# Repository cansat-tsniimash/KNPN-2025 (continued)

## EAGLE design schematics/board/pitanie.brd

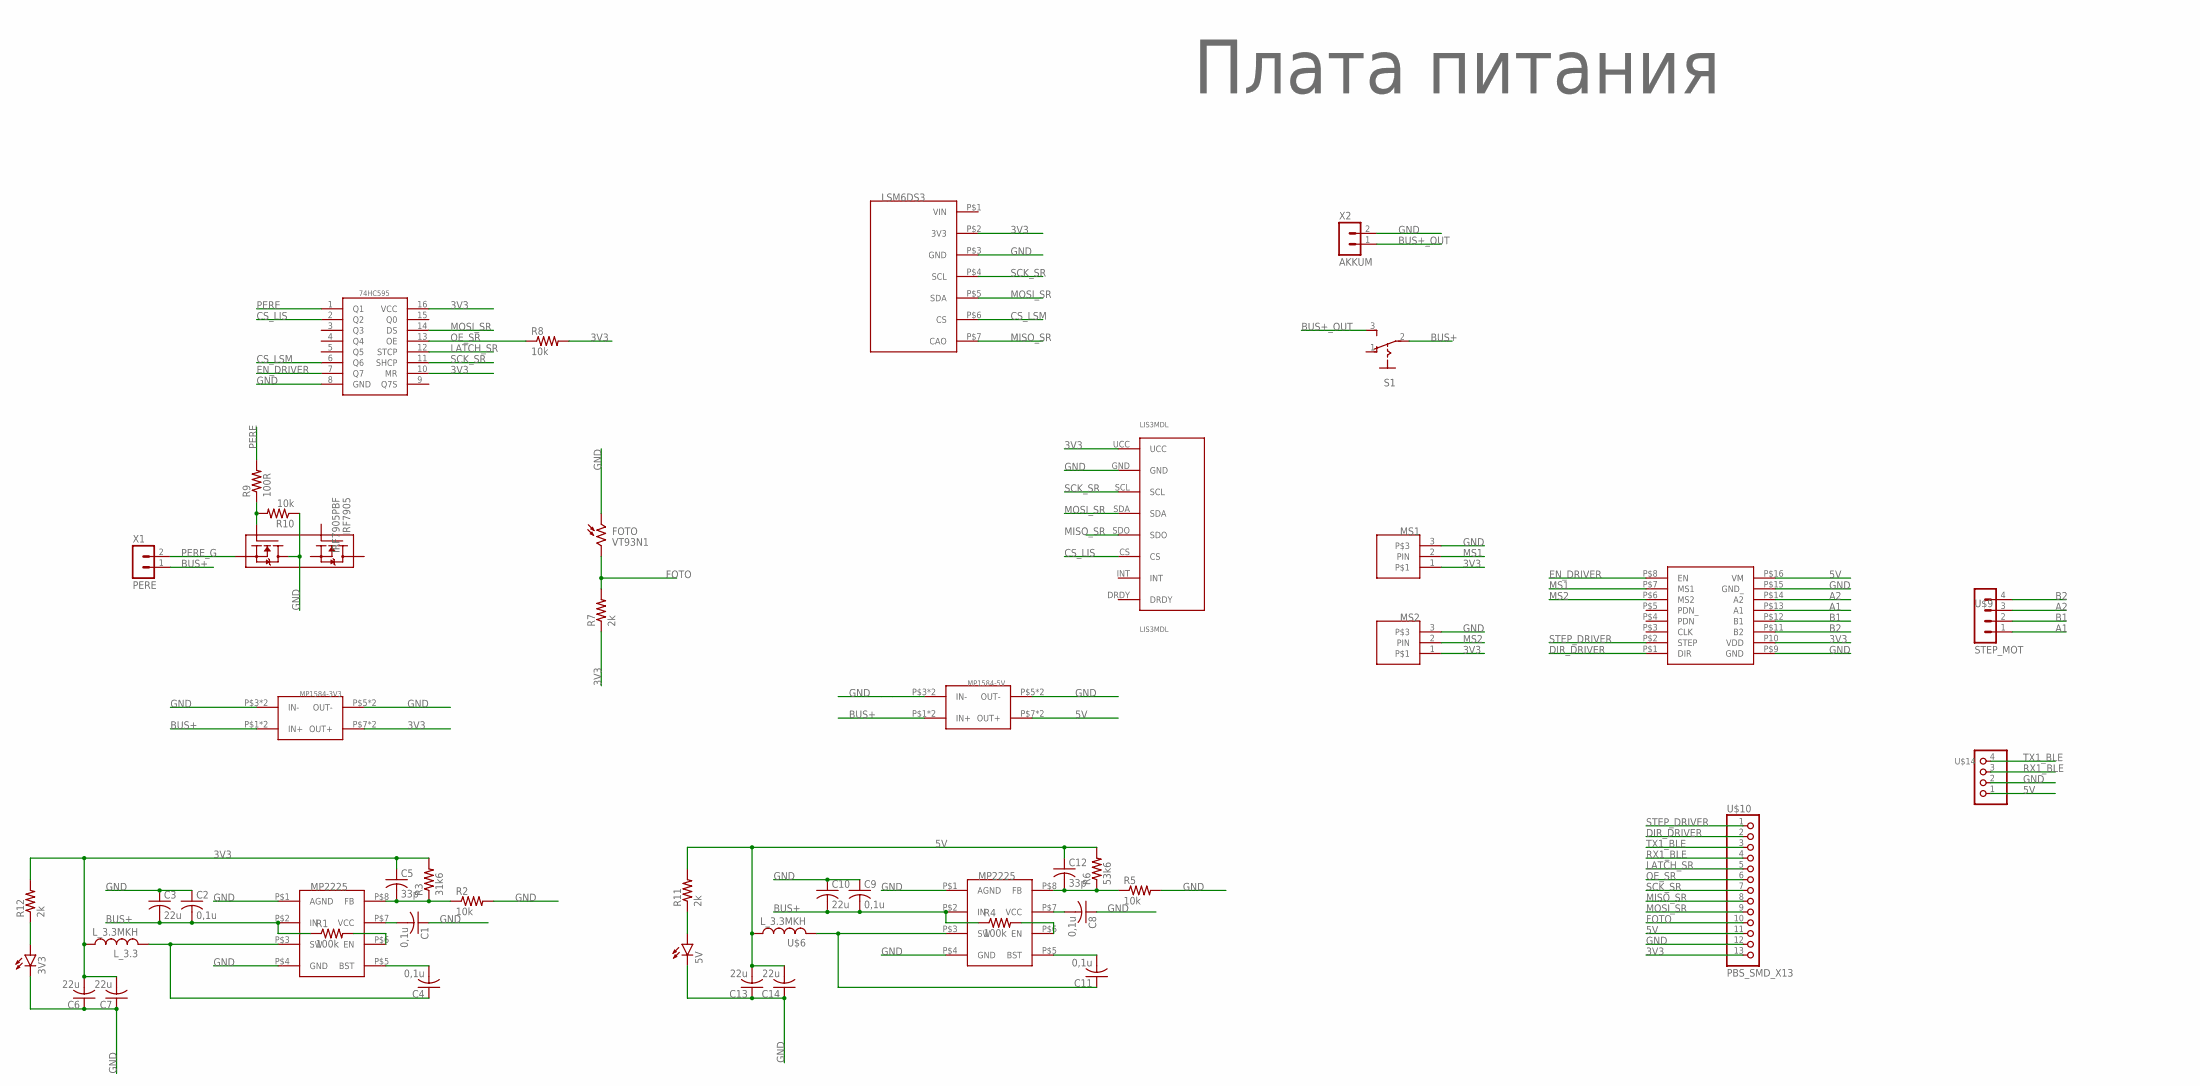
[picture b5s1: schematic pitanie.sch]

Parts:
3V3, 5V: LEDCHIP-LED0603; CHIP-LED0603
74HC595: 74HC595; TSSOP16
C1, C4, C8, C11: 0,1u; C0603
C2, C9: 0,1u; C1206
C3, C10: 22u; C0603
C5, C12: 33p; C0603
C6, C7, C13, C14: 22u; C1206
DRIVER: TMC2209_WITHOUT
FOTO: VT93N1
IRF7905: IRF7905PBF; SO8
LIS3MDL: LIS3MDL
LSM6DS3: LSM6DS3_WITHOUT
L_3.3: L_3.3MKH; L_SPM5020
MP1584-3V3: MP1584-B
MP1584-5V: MP1584; MP1584-B
MS1, MS2: CONNECT_3
R1, R4: 100k; R0603
R2, R5, R8, R10: 10k; R0603
R3: 31k6; R0603
R6: 53k6; R0603
R7, R11, R12: 2k; R0603
R9: 100R; R0603
S1: UNICS-SWITCHSS_12D11; SS_12D11
U$1: Плата питания; LOGO
U$2, U$5: MP2225; TSOT23-8
U$6: L_3.3MKH; L_SPM5020
U$9: STEP_MOT; JST-4-2.5
U$10: PBS_SMD_X13; PBD_SMD_X13
U$14: BLUETOOTH; 53047-04
X1: PERE; JST-2-2.5
X2: AKKUM; JST-2-2.5

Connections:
3V3: 74HC595.10 (MR), 74HC595.16 (VCC), C5.1, C6.2, C7.2, DRIVER.P10 (VDD), LIS3MDL.UCC, LSM6DS3.P$2 (3V3), L_3.3.P$1 (1), MP1584-3V3.P$7 (OUT+), MP1584-3V3.P$8 (OUT+), MS1.1, MS2.1, R3.2, R7.1, R8.2, R12.2, U$10.13
5V: C12.1, C13.2, C14.2, DRIVER.P$16 (VM), MP1584-5V.P$7 (OUT+), MP1584-5V.P$8 (OUT+), R6.2, R11.2, U$6.P$1 (1), U$10.11, U$14.1
A1: DRIVER.P$13 (A1), U$9.1
A2: DRIVER.P$14 (A2), U$9.3
B1: DRIVER.P$12 (B1), U$9.2
B2: DRIVER.P$11 (B2), U$9.4
BUS+: C2.2, C3.2, C9.2, C10.2, MP1584-3V3.P$1 (IN+), MP1584-3V3.P$2 (IN+), MP1584-5V.P$1 (IN+), MP1584-5V.P$2 (IN+), R1.1, R4.1, S1.2, U$2.P$2 (IN), U$5.P$2 (IN), X1.1
BUS+_OUT: S1.3 (S), X2.1
CS_LIS: 74HC595.2 (Q2), LIS3MDL.CS
CS_LSM: 74HC595.6 (Q6), LSM6DS3.P$6 (CS)
DIR_DRIVER: DRIVER.P$1 (DIR), U$10.2
EN_DRIVER: 74HC595.7 (Q7), DRIVER.P$8 (EN)
FOTO: FOTO.P$2 (2), R7.2, U$10.10
GND: 3V3.C, 5V.C, 74HC595.8 (GND), C1.1, C2.1, C3.1, C6.1, C7.1, C8.1, C9.1, C10.1, C13.1, C14.1, DRIVER.P$9 (GND), DRIVER.P$15 (GND_), FOTO.P$1 (1), IRF7905.7 (D2), IRF7905.8 (D2), LIS3MDL.GND, LSM6DS3.P$3 (GND), MP1584-3V3.P$3 (IN-), MP1584-3V3.P$4 (IN-), MP1584-3V3.P$5 (OUT-), MP1584-3V3.P$6 (OUT-), MP1584-5V.P$3 (IN-), MP1584-5V.P$4 (IN-), MP1584-5V.P$5 (OUT-), MP1584-5V.P$6 (OUT-), MS1.3, MS2.3, R2.2, R5.2, R10.1, U$2.P$1 (AGND), U$2.P$4 (GND), U$5.P$1 (AGND), U$5.P$4 (GND), U$10.12, U$14.2, X2.2
LATCH_SR: 74HC595.12 (STCP), U$10.5
MISO_SR: LIS3MDL.SDO, LSM6DS3.P$7 (CAO), U$10.8
MOSI_SR: 74HC595.14 (DS), LIS3MDL.SDA, LSM6DS3.P$5 (SDA), U$10.9
MS1: DRIVER.P$7 (MS1), MS1.2 (PIN)
MS2: DRIVER.P$6 (MS2), MS2.2 (PIN)
unnamed: C1.2, U$2.P$7 (VCC)
unnamed: R1.2, U$2.P$6 (EN)
unnamed: C4.2, U$2.P$5 (BST)
unnamed: C4.1, L_3.3.P$2 (2), U$2.P$3 (SW)
unnamed: C5.2, R2.1, R3.1, U$2.P$8 (FB)
unnamed: IRF7905.2 (G2), R9.1, R10.2
unnamed: C8.2, U$5.P$7 (VCC)
unnamed: R4.2, U$5.P$6 (EN)
unnamed: C11.2, U$5.P$5 (BST)
unnamed: C11.1, U$5.P$3 (SW), U$6.P$2 (2)
unnamed: C12.2, R5.1, R6.1, U$5.P$8 (FB)
unnamed: 5V.A, R11.1
unnamed: 3V3.A, R12.1
OE_SR: 74HC595.13 (OE), R8.1, U$10.6
PERE: 74HC595.1 (Q1), R9.2
PERE_G: IRF7905.1 (S2), X1.2
RX1_BLE: U$10.4, U$14.3
SCK_SR: 74HC595.11 (SHCP), LIS3MDL.SCL, LSM6DS3.P$4 (SCL), U$10.7
STEP_DRIVER: DRIVER.P$2 (STEP), U$10.1
TX1_BLE: U$10.3, U$14.4

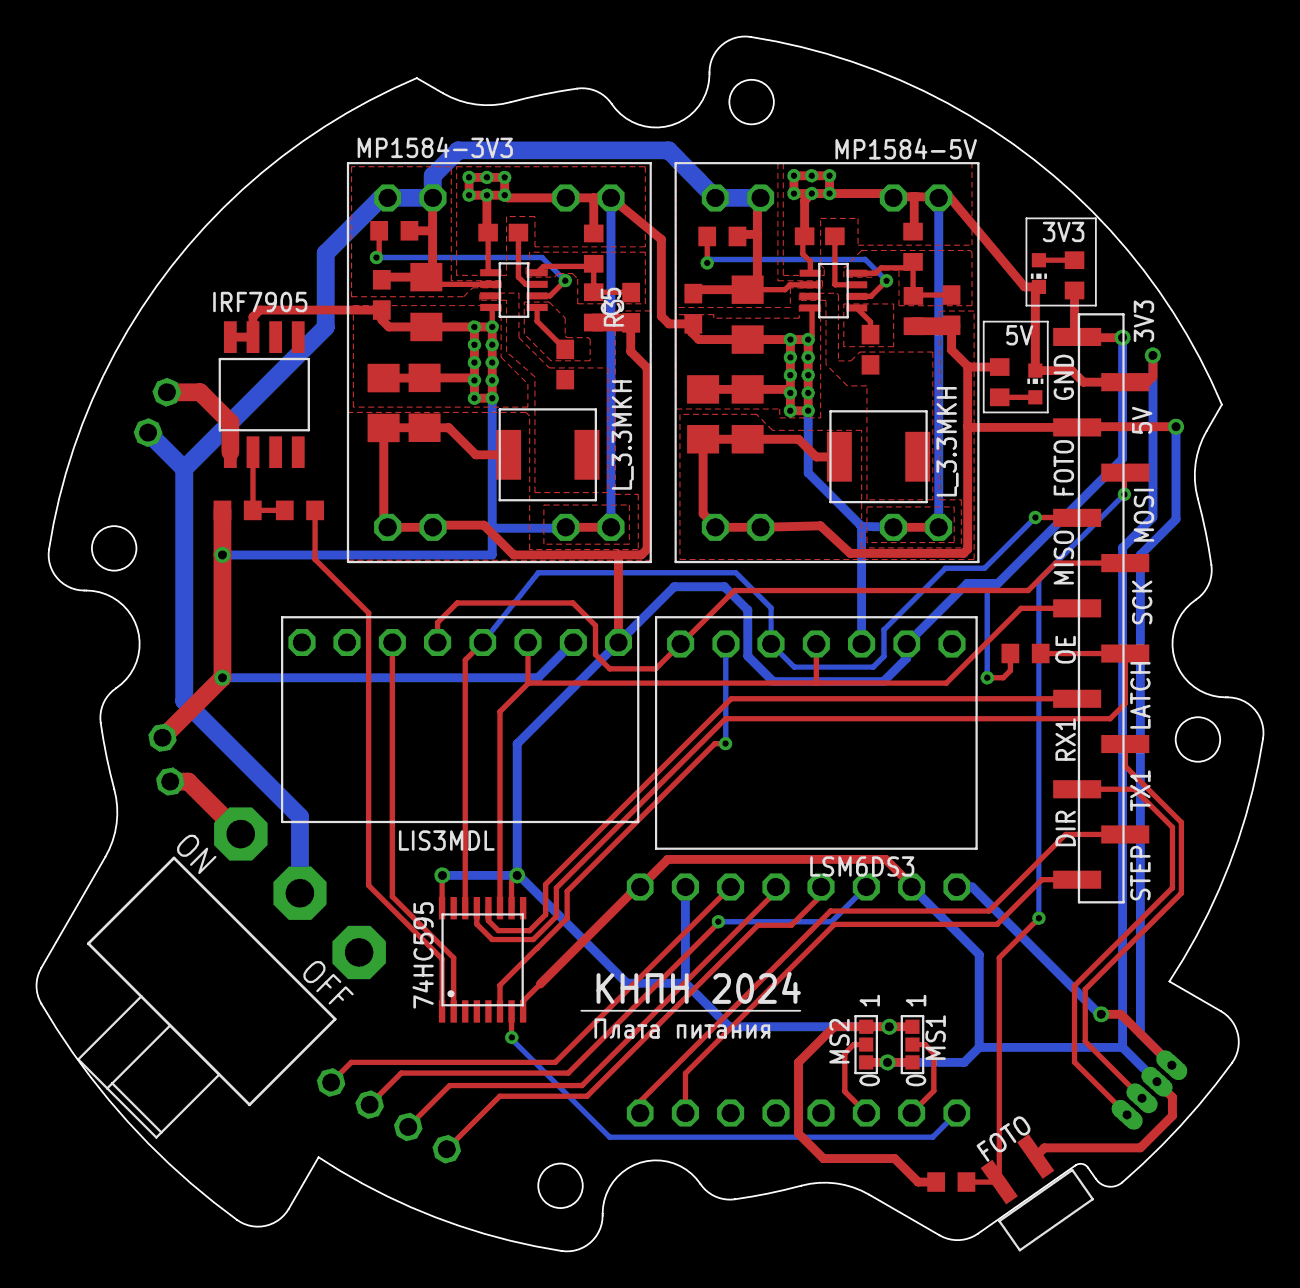
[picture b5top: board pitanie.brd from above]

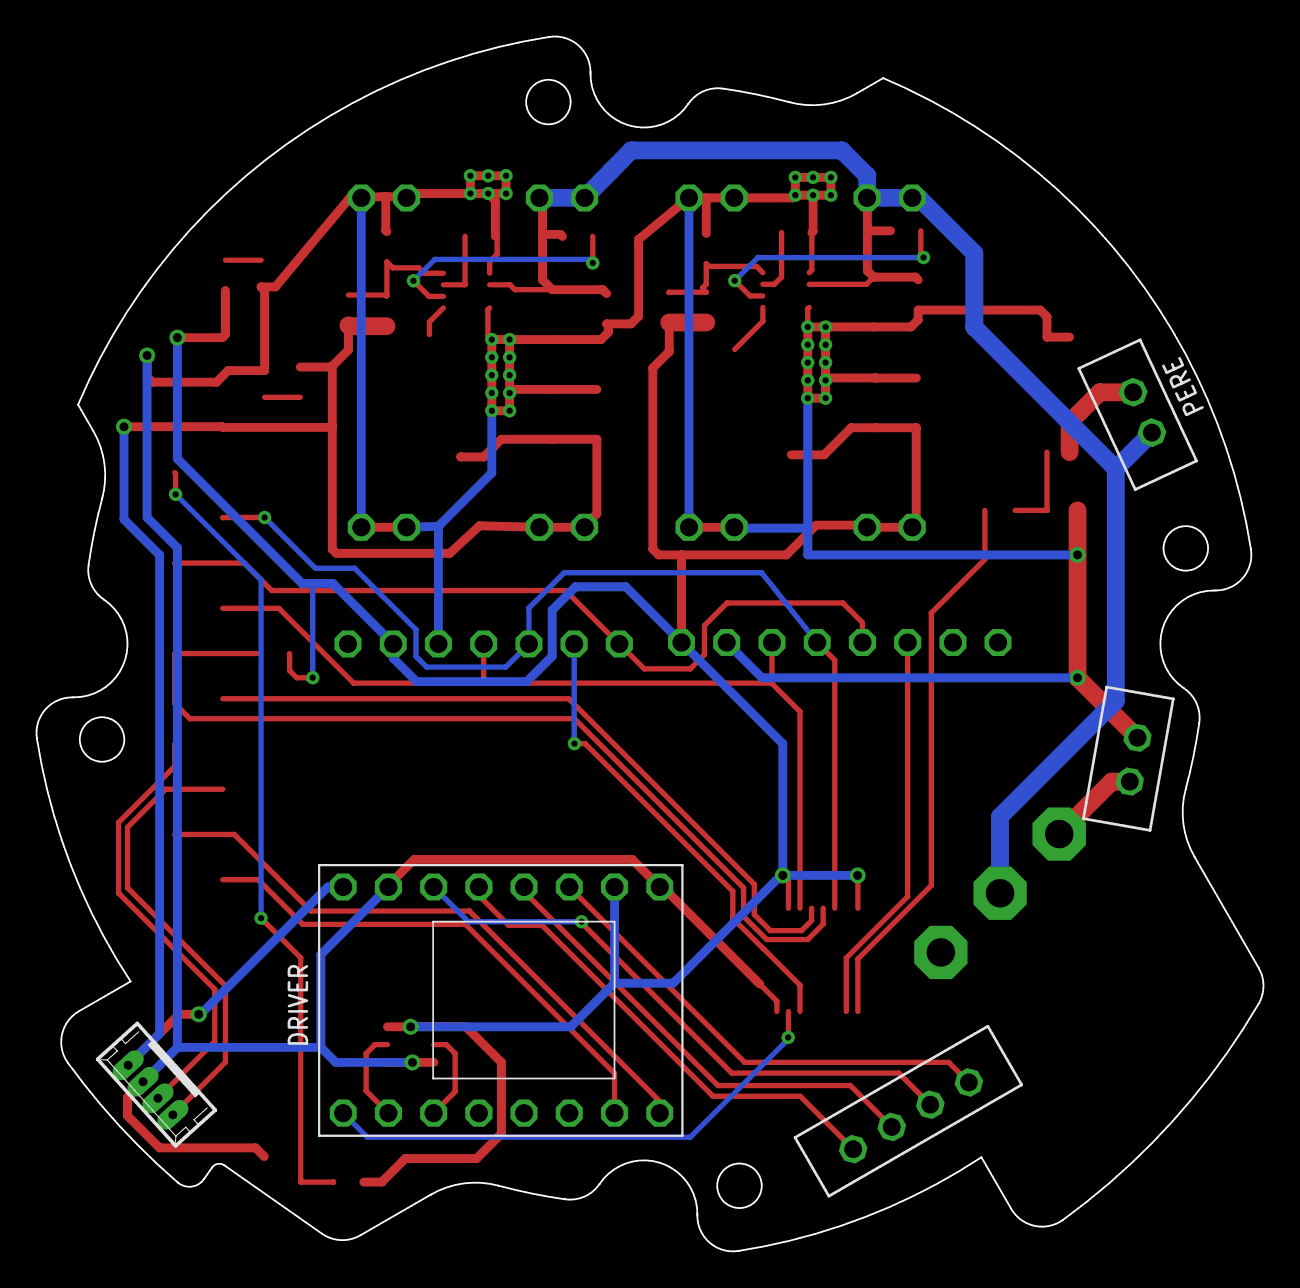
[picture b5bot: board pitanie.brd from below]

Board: 2 copper layers, 68.9 x 68.2 mm, 49 parts (5 on the bottom side), 39 nets.
